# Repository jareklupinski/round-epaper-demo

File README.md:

# round-epaper-demo
Breakout board and example code for driving a round e-ink display

Work in progress, just got the basics down before digging into it.

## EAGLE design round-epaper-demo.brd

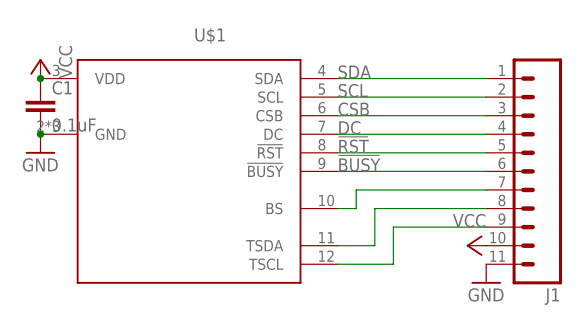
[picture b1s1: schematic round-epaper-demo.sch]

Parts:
C1: 0.1uF; 0603-CAP
J1: M11PTH; 1X11
U$1: GDEP011TT2; FH26W-15S-0.3S

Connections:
!BUSY: J1.6, U$1.9 (!BUSY)
!RST: J1.5, U$1.8 (!RST)
BS: J1.7, U$1.10 (BS)
CSB: J1.3, U$1.6 (CSB)
DC: J1.4, U$1.7 (DC)
GND: C1.2, J1.11, U$1.2 (GND), U$1.EXP1 (GND), U$1.EXP2 (GND)
SCL: J1.2, U$1.5 (SCL)
SDA: J1.1, U$1.4 (SDA)
TSCL: J1.9, U$1.12 (TSCL)
TSDA: J1.8, U$1.11 (TSDA)
VCC: C1.1, J1.10, U$1.3 (VDD)

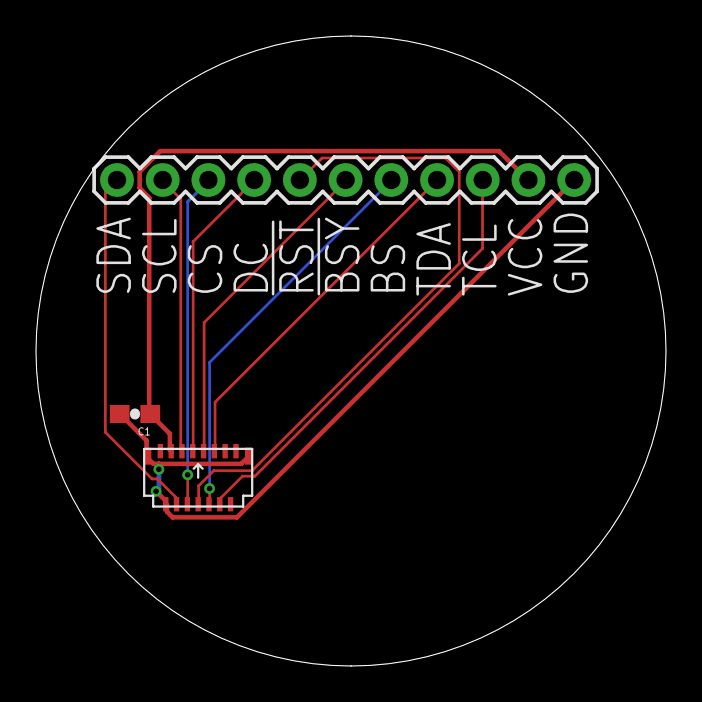
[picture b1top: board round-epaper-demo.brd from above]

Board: 2 copper layers, 35.0 x 35.0 mm, 3 parts (0 on the bottom side), 11 nets.

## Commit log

2018-07-05 work in progress

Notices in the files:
parts and their libraries:
SparkFun-Capacitors: Licensing: CC v3.0 Share-Alike You are welcome to use this library for commercial purposes.
SparkFun-Connectors: Licensing: Creative Commons ShareAlike 4.0 International - https://creativecommons.org/licenses/by-sa/4.0
